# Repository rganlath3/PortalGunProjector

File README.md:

# Portal Gun Embedded Projector

A Portal Gun prop featuring an embedded HDMI projector that displays authentic Portal visuals and sounds. This project combines 3D printing, electronics, and software to create a realistic prop that doubles as a portable projector. The portal gun is from popular Valve videogame, Portal / Portal 2.

<!-- TABLE OF CONTENTS -->
## Table of Contents

<details>
<summary>Table of Contents</summary>

1. [About The Project](#about-the-project)
    - [Design Tools & Requirements](#design-tools--requirements)
        - [Software Requirements](#software-requirements)
        - [Hardware Requirements](#hardware-requirements)
2. [Hardware Development](#hardware-development)
    - [Bill of Materials](#bill-of-materials)
    - [Hardware Used](#hardware-used)
    - [3D Printing the Model](#3d-printing-the-model)
    - [3D Printing Specifications](#3d-printing-specifications)
    - [Model Prep](#model-prep)
    - [Electrical Interconnect Diagram](#electrical-interconnect-diagram)
    - [PCB](#pcb)
    - [Wiring](#wiring)
    - [Power](#power)
3. [Software Development](#software-development)
4. [Getting Started](#getting-started)
    - [Prerequisites](#prerequisites)
    - [Installation](#installation)
    - [Common Issues](#common-issues)
5. [Assets](#assets)
    - [Audio](#audio)
    - [Video](#video)
6. [Roadmap](#roadmap)
7. [Contributing & Donations](#contributing--donations)
8. [License](#license)
9. [Contact](#contact)

</details>

<!-- ABOUT THE PROJECT -->
## About The Project
The idea was to take 3D printing a Portal Gun Prop to the next level of realism. My brother inspired me to create a Prop Portal Gun with an full HDMI Projector inside of the prop. When activated, it displays authentic Portal visuals, produces game-accurate sound effects through integrated speakers, and displays LED effects. The project combines 3D printing, electronics, and software development to create a prop that's both visually accurate and practically useful as a portable projector.

### Design Tools & Requirements

#### Software Requirements
- Python 3.9+ (Programming Language for RPi)
- Raspberry Pi OS Debian v12 (64-bit)
- VS Code (Programming IDE)
- Autodesk Fusion360 (Free CAD Software)
- KiCAD 7 (Open Source PCB Design Software)
- Ultimaker Cura (Free 3D Slicing Software)

#### Hardware Requirements
- Raspberry Pi 4 (8GB RAM recommended)
- 32GB+ SD Card
- 12V Power Supply or 4S Lipo Battery Pack

<p align="right">(<a href="#readme-top">back to top</a>)</p>

## Hardware Development

### Bill of Materials
Coming Soon

### Hardware Used
* Raspberry Pi 4 (SBC)
* Custom RPi HAT PCB (Power and GPIO Distribtuion to Screw Terminals) (See PCB Designs)
* Various Capacitors, Resistors, SMD LEDs, JST Connectors, Wire Crimps, etc.
* Various stranded wire lengths and colors: 16AWG, 22AWG.
* 1x DROK 9V-24V to 5V Step Down Buck Converter, 30W (Powers Pi from Battery Input)
* 1x Songhe 10-32V to 21V Step Up Boost Converter, 150W (Powers Projector from Battery Input)
* 1x 16mm Momentary Metal LED Push Button (Orange)
* 1x 16mm Momentary Metal LED Push Button (Blue)
* 2x 2.1mm DC Barrel Jacks Pair (Power Input)
* 2x SPST 20A Heavy Duty Toggle Switch (Projector Power and Pi Power)
* 1x SPST 5A Mini Toggle Switch (LED Power)
* 1x Individually Addressable 5V NeoPixel
* 1x 1ft. RGB COB Individually Addressable 5V LED Strip 
* Portal Gun 3D Design: (found on thingiverse [here](https://www.thingiverse.com/thing:3579224)) 
* My modifications to the Portal Gun 3D Design.
* 3D Printer: Creality CR-10SProV2

### 3D Printing the Model
I used this portal gun design as a basis for my version. This creator put a lot of work into his design so please give him the attention he deserves: [EVARATE Portal Gun](https://www.thingiverse.com/thing:3579224)

### 3D Printing Specifications

#### Print Settings
- Layer Height: 0.2mm
- Infill: 15% for most parts but 100% for finger parts
- Temperature: 210°C (PLA+)
- Build Plate: 60°C
- Support: Required for overhangs
- Material: eSUN PLA+ or equivalent

Besides modifying parts to fit the projector, I also designed an electronics sled to fit the handle base. This is what the DC-DC converters and Raspberry Pi mount to.

### Model Prep
Sanding, filler, painting, etc.

* 3M Acryl Putty, 05096 Green or 05098 Red
* Various Sandpaper and Sanding Sponges
* Dremel
* P95 or Better Respirator (don't cheap out on this)
* Filler & Sandable Primer (I use cheap Rust-Oleum)
* Montana Gold Shock White Pure Spray Paint
* Montana Gold Shock Black Spray Paint
* Spray Max USC 2K High Gloss Clearcoat (Automotive Clearcoat, expensive but worth it!)

Once all the parts have been printed, we need to do some post processing to get the prints as smooth as possible. For my first iteration, I used a dremel to manually cut holes in some parts instead of just CADing them out. (I wasn't sure how things would exactly fit.)

*Note: Anytime we are sanding or spray painting, you MUST be wearing that respirator! 
Also try to handle all the parts with rubber gloves so your fingerprints don't mess up the paint coats.*

Using sanding paper and sponges I used the following grits:
120->220->320->400 using spot putty where needed. Anything above 320 grit should be wet sanded. Then 2x coats of fillable primer spray paint. Then 400 grit. Then 1x coat of fillable primer. Then one more 400 grit. Then 600 grit. Then apply desired paint color (black and white) base coat in many light coats. (3-5 coats) I'd like to try to find an alternate to Montana Gold.

Once fully dried, use a damp sponge and wipe the parts. Use 1000 grit to sand down the base coat. 

Optional: Using citadel paints or any acrylic paints, add weathering, scuff marks, or damage. I ended up using a metal file and creating scratches. I finely dry brushed silver paint onto the black parts to create a metallic highlight effect. I also added a white line on the top white part.

Once finished painting, we can now apply layers of clearcoat in a very well ventilated area. This 2K stuff is really toxic so be careful. I ended up using rust-oleum 2x ultracover clear instead which gave a good result but not as nice as 2k would have been. I used gloss clear coat on the white parts and black arms. I used matte clear coat on the black parts. Once fully cured, assembly can begin.

### Electrical Interconnect Diagram

### PCB
I designed a Raspberry Pi Hat PCB that handles powering the board (via 5V pins), powering LEDs, and acting as GPIO inputs/outputs for button inputs and driving neopixels. See Mk2 design for the latest. If I had a chance for another iteration, I would add slotted holes in the center section for the placement of a low profile fan for cooling the raspberry pi.

### Wiring
I used 22AWG and 16AWG for all wiring in the system. 22AWG was used for neopixels and GPIO pins while 16AWG was used for all power lines. 
* Red - Power
* Black - GND
* Green - Data / GPIO

### Power
I have two separate power circuits: Pi and Projector.

The Pi Circuit runs on 5V. It powers the neopixels, raspberry pi, and push button LEDs.
* Input Voltage: 12V
* Converted Voltage: 5V
* Average Wattage (Script Running): 4.1W
* Theorhetical Max Load: 
* Safety Factor (Max Power * 1.25W): 7W
* Battery Required for 2 hour battery life:

The Projector Circuit runs on 21V. It powers the projector and it's internal speakers.
* Input Voltage: 12V
* Converted Voltage: 21V
* Average Watage (Lamp On): 41.46W
* Theorhetical Max Load:
* Safety Factor (Max Power * 1.25W): 53W
* Battery Required for 2 hour battery life:

## Software Development
I am familiar using an Arduino or other MCU to solve all my hardware integration problems. In the past I've used Arduinos + Raspberry Pis when needed (such as for ROS projects). For this project, I wanted to challenge myself to not use any MCUs and to only use the raspberry pi GPIO pins to interact with switches and LED control. It brought up some fun compatibility issues that prevented me from using a Raspberry Pi 5 until libraries were updated. 

***Disclaimer: I am an electrical engineer, so apologies for the chaos that is my programming.***

<!-- GETTING STARTED -->
## Getting Started

* Install Raspberry Pi OS with Desktop (Debian v12) (64-bit)
  * we will use the desktop version for initial setup then switch to the CLI for actual operation. This saves time when troubleshooting things like VLC issues.
* Copy this repo to any desired folder. 
  * For reference, my filepath was: */home/aperture/Documents/PortalGunProjector*

### Prerequisites
*Note: Since Neopixel Usage requires root priviledges, make sure your environment path is configured accordingly. I recommend installing all these python libraries as root (sudo command). It is possible to run sudoless but it requires using only GPIO10 for LEDs*

```bash
# Update System
sudo apt update && sudo apt upgrade -y

# Install Required Packages
sudo apt install git python3-pip vlc -y

# Install Python Dependencies

# Raspberry PI GPIO Control
sudo pip3 install gpiozero

# NeoPixel Drivers
sudo pip3 install adafruit-circuitpython-neopixel

# Pygame
sudo pip3 install pygame

# VLC
sudo apt install vlc

# VLC Python Bindings
sudo pip3 install python-vlc
```

### Installation

1. If you haven't already, clone the repo, to a directory such as: */home/username/Documents/PortalGunProjector*

   ```sh
   git clone https://github.com/rganlath3/PortalGunProjector.git
   ```
2. Install prequisites listed above.

3. Run each test script to test functionality as you build, then run launch.py

<p align="right">(<a href="#readme-top">back to top</a>)</p>

### Common Issues

1. LED Control Fails
```bash
# Check permissions
sudo usermod -a -G gpio $USER
# Reboot required after permission change
```

2. Video Playback Issues
- Ensure micro HDMI port used is closest to USB-C power connector.
- Check video codec compatibility
- Verify file permissions

## Assets

### Audio
The portal gun plays audio out of the hdmi audio output via the projector speakers. Everytime a button is pressed, a random soundclip from a list will play to add some variety to mashing buttons. All audio files are in the "Sounds" folder and are extracted from in game. I do not own these files.

### Video
On bootup a random video and audio line will play as an initialization. On button presses, a random sized orange or blue portal video will play on loop. I manually created these videos by screen recording Garry's Mod and careful editing. Bootup videos are sourced from Portal Gameplay and Trailers from Value and are not owned by me. 

<!-- ROADMAP -->
## Roadmap
- [x] CAD Small Projector
- [x] Modify Portal Gun Designs
- [x] Design electrical interconnect
- [x] 3D Print all parts
- [x] Sanding and post processing on parts
- [x] Painting all parts
- [x] Redesign electrical interconnect
- [x] Create Electronics Sled
- [x] Create wiring harness
- [x] Test LED effects
- [x] Integrate pushbuttons into programming
- [x] Create portal and bootup videos
- [x] Configure code to run on startup
- [x] Add Visual Documentation to GitHub
- [x] Assemble Portal Gun
- [x] Final tests with benchtop power supply
- [ ] Add magnets and external cables
- [ ] Create Battery Harness

<p align="right">(<a href="#readme-top">back to top</a>)</p>

<!-- CONTRIBUTING -->
## Contributing & Donations

Any donation helps to support parts for future open source projects!
[Buy Me a Coffee ☕](https://www.buymeacoffee.com/rganlath)

Contributions are what make the open source community such an amazing place to learn, inspire, and create. Any contributions you make are **greatly appreciated**.

If you have a suggestion that would make this better, please fork the repo and create a pull request. You can also simply open an issue with the tag "enhancement".
Don't forget to give the project a star! Thanks again!

<p align="right">(<a href="#readme-top">back to top</a>)</p>

<!-- LICENSE -->
## License
The contents of this project itself is licensed under CERN-OHL-S-2.0 and the underlying source code used for programming the raspberry pi is licensed under GNU GPLv3. Both of these licenses require attribution.

<p align="right">(<a href="#readme-top">back to top</a>)</p>

<!-- CONTACT -->
## Contact

Ranil Ganlath - ranil.ganlath@gmail.com

Project Link: [https://github.com/rganlath3/PortalGunProjector](https://github.com/rganlath3/PortalGunProjector)

<p align="right">(<a href="#readme-top">back to top</a>)</p>

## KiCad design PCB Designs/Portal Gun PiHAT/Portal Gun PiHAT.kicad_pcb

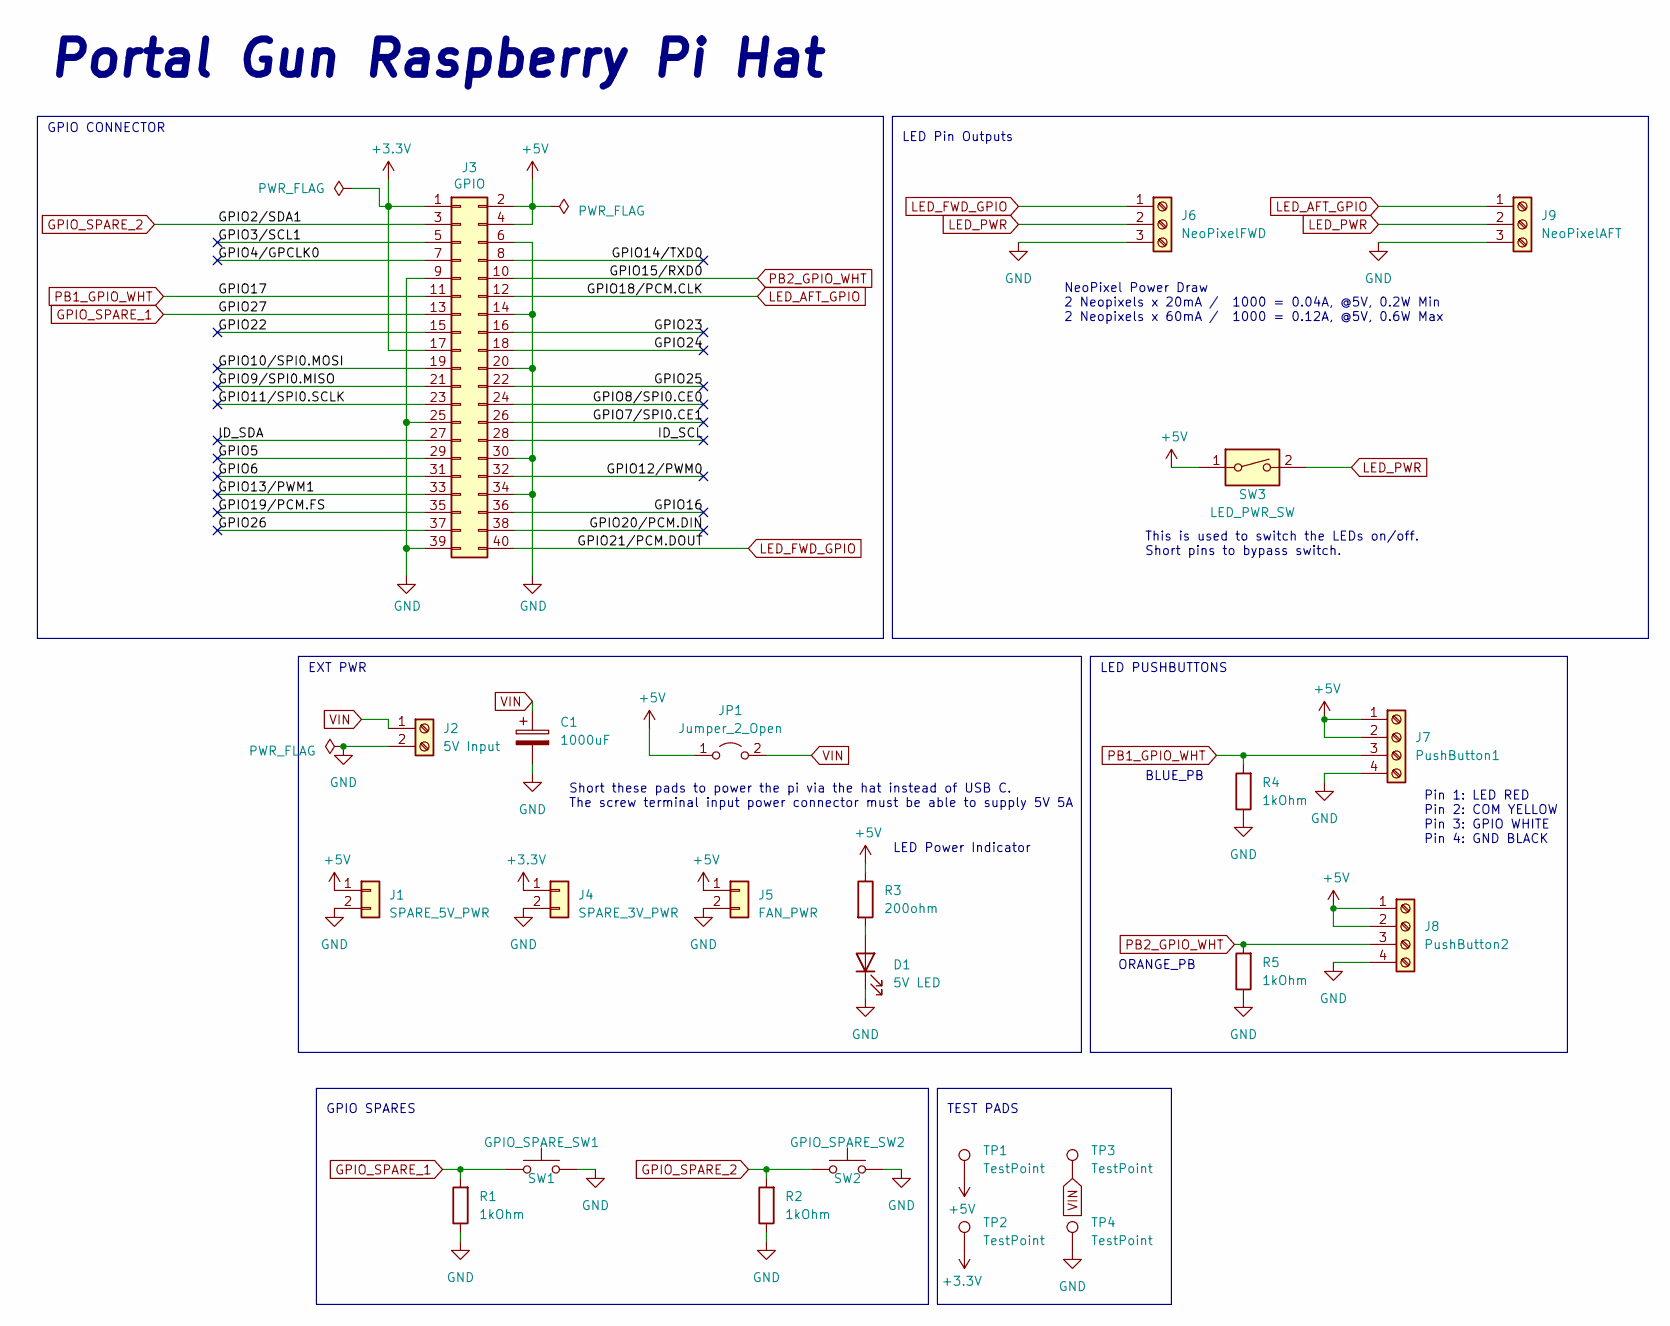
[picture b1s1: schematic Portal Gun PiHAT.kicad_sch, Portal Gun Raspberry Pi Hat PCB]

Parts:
C1: 1000uF; C_Radial_D10.0mm_H16.0mm_P5.00mm
D1: 5V LED; LED_D3.0mm
J1: SPARE_5V_PWR; PinHeader_1x02_P2.54mm_Vertical
J2: 5V Input; TerminalBlock_Phoenix_MKDS-1,5-2_1x02_P5.00mm_Horizontal
J3: GPIO; PinSocket_2x20_P2.54mm_Vertical
J4: SPARE_3V_PWR; PinHeader_1x02_P2.54mm_Vertical
J5: FAN_PWR; PinHeader_1x02_P2.54mm_Vertical
J6: NeoPixelFWD; TerminalBlock_Phoenix_MKDS-1,5-3_1x03_P5.00mm_Horizontal
J7: PushButton1; TerminalBlock_Phoenix_MKDS-1,5-4_1x04_P5.00mm_Horizontal
J8: PushButton2; TerminalBlock_Phoenix_MKDS-1,5-4_1x04_P5.00mm_Horizontal
J9: NeoPixelAFT; TerminalBlock_Phoenix_MKDS-1,5-3_1x03_P5.00mm_Horizontal
JP1: Jumper_2_Open; SolderJumper-2_P1.3mm_Open_Pad1.0x1.5mm
R1, R2, R4, R5: 1kOhm; R_1206_3216Metric_Pad1.30x1.75mm_HandSolder
R3: 200ohm; R_1206_3216Metric_Pad1.30x1.75mm_HandSolder
SW1: GPIO_SPARE_SW1; PinHeader_1x02_P2.54mm_Vertical
SW2: GPIO_SPARE_SW2; PinHeader_1x02_P2.54mm_Vertical
SW3: LED_PWR_SW; PinHeader_1x02_P2.54mm_Vertical
TP1, TP2, TP3, TP4: TestPoint; TestPoint_Pad_D1.0mm

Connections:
+3V3: J3.1, J3.17, J4.1, TP2.1
+5V: J1.1, J3.2, J3.4, J5.1, J7.1, J7.2, J8.1, J8.2, JP1.1 (A), R3.1, SW3.1, TP1.1
/GPIO3/SCL1: J3.5
/GPIO4/GPCLK0: J3.7
/GPIO5: J3.29
/GPIO6: J3.31
/GPIO7/SPI0.CE1: J3.26
/GPIO8/SPI0.CE0: J3.24
/GPIO9/SPI0.MISO: J3.21
/GPIO10/SPI0.MOSI: J3.19
/GPIO11/SPI0.SCLK: J3.23
/GPIO12/PWM0: J3.32
/GPIO13/PWM1: J3.33
/GPIO14/TXD0: J3.8
/GPIO16: J3.36
/GPIO19/PCM.FS: J3.35
/GPIO20/PCM.DIN: J3.38
/GPIO22: J3.15
/GPIO23: J3.16
/GPIO24: J3.18
/GPIO25: J3.22
/GPIO26: J3.37
/ID_SCL: J3.28
/ID_SDA: J3.27
GND: C1.2, D1.1 (K), J1.2, J2.2, J3.6, J3.9, J3.14, J3.20, J3.25, J3.30, J3.34, J3.39, J4.2, J5.2, J6.3, J7.4, J8.4, J9.3, R1.1, R2.1, R4.1, R5.1, SW1.2, SW2.2, TP4.1
GPIO_SPARE_1: J3.13, R1.2, SW1.1
GPIO_SPARE_2: J3.3, R2.2, SW2.1
LED_AFT_GPIO: J3.12, J9.1
LED_FWD_GPIO: J3.40, J6.1
LED_PWR: J6.2, J9.2, SW3.2
unnamed: D1.2 (A), R3.2
PB1_GPIO_WHT: J3.11, J7.3, R4.2
PB2_GPIO_WHT: J3.10, J8.3, R5.2
VIN: C1.1, J2.1, JP1.2 (B), TP3.1

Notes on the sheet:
LED Power Indicator
This is used to switch the LEDs on/off. Short pins to bypass switch.
GPIO CONNECTOR
LED PUSHBUTTONS
Portal Gun Raspberry Pi Hat
NeoPixel Power Draw 2 Neopixels x 20mA / 1000 = 0.04A, @5V, 0.2W Min 2 Neopixels x 60mA / 1000 = 0.12A, @5V, 0.6W Max
BLUE_PB
ORANGE_PB
LED Pin Outputs
GPIO SPARES
Short these pads to power the pi via the hat instead of USB C. The screw terminal input power connector must be able to supply 5V 5A
Pin 1: LED RED Pin 2: COM YELLOW Pin 3: GPIO WHITE Pin 4: GND BLACK
TEST PADS
EXT PWR

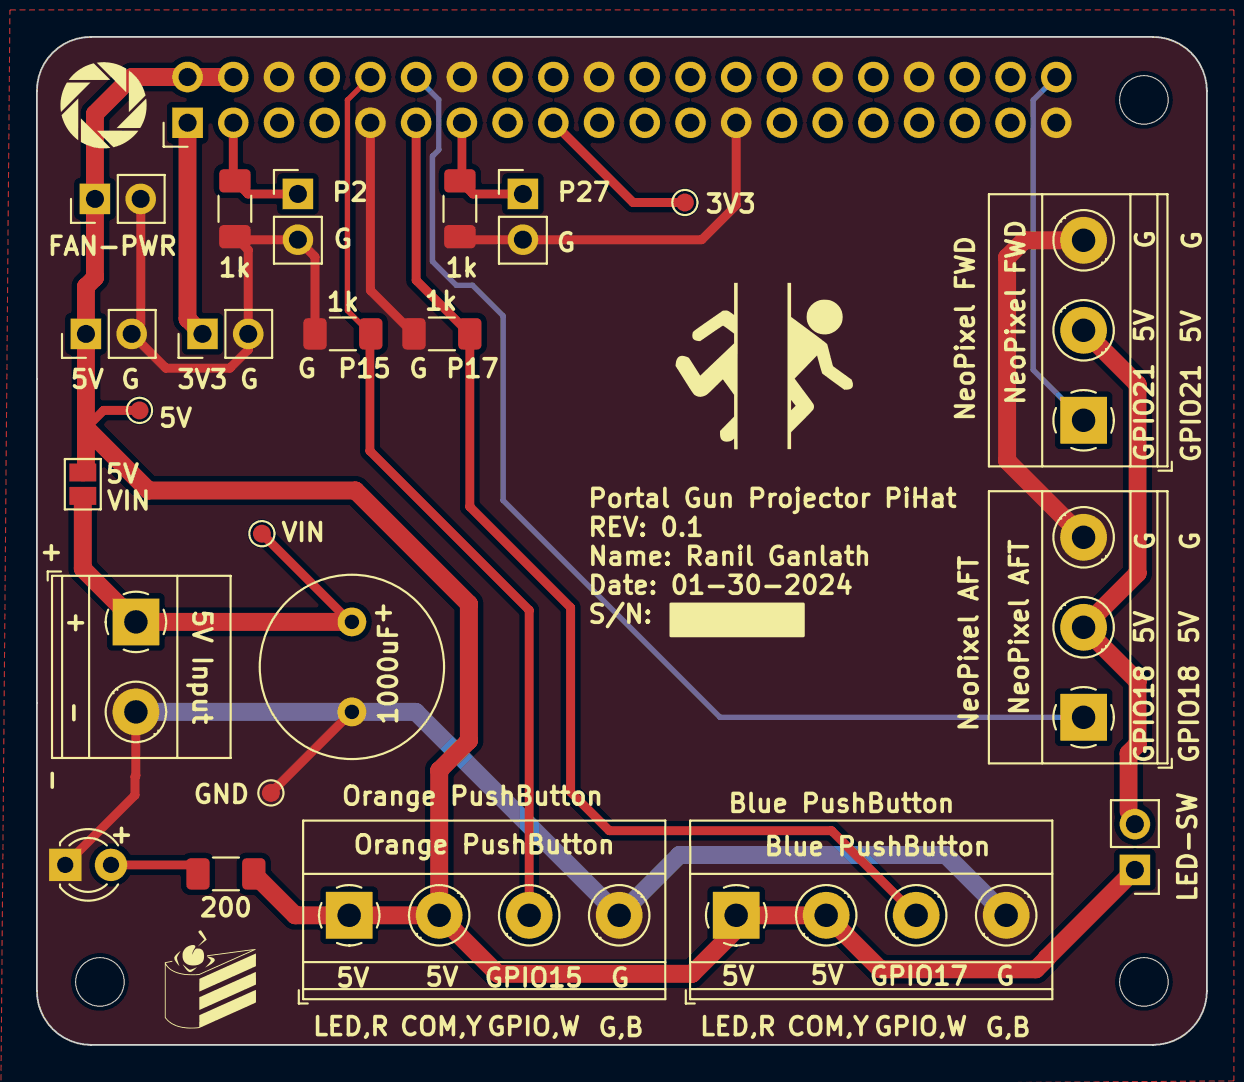
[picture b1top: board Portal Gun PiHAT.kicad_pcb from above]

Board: 2 copper layers, 65.0 x 56.0 mm, 27 parts (1 on the bottom side), 12 nets.

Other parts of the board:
MH2, MH3, MH4: MountingHole_2.7mm_M2.5

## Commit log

2024-01-23 Initial Project Creation
2024-01-23 Added parts from prior kiKAD projects
2024-01-25 schematic updates
2024-01-31 KiCad PCBs Finalized
2024-01-31 Audio File Upload
2024-01-31 Test Script Creation
2024-02-23 PCB Design Updates to fix name formatting and 3V GPIO correction on pushbuttons
2024-03-20 Updated for longer LED chain
2024-03-20 Button Fixes
2024-03-26 Renamed Audio Files
2024-03-26 Added new led animations
2024-03-27 Added new animations and audio sounds
2024-03-27 Added new sounds effects
2024-03-28 Changed format of some sounds to be .wav
2024-03-29 Incorporated new bootup sounds, need to add queue thingy.
2024-03-29 Added bootup animation based on sound file played.
2024-04-03 Created scripts that start on bootup.
2024-04-03 Changed naming convention and added comments
2024-04-03 Starting Video PlayBack Tests
2024-04-03 Portal Looping Animations
2024-04-04 Testing VideoPlayBack. Need to find VLC commands or alt.
2024-04-08 Testing out python-vlc library.
2024-04-09 finally got vlc working smoothly, just need to roll into main script.
2024-04-09 working but no fullscreen
2024-04-09 it works! just needs cleanup
2024-04-10 Finally got VLC fully working with audio track
2024-04-10 Updated launch script to handle if pi is in cli or gui mode accordingly.
2024-04-10 Testing PathLib
2024-04-11 Created bootup videos
2024-04-11 Added Bootup Video and Relative File Paths
2024-04-11 Debug command to turn off LEDs added
2024-04-11 trying to make code launch on bootup in both cli and desktop environments
2024-04-12 Updated with model prep info.
2024-04-12 Updates to readme and project cleanup.
2024-12-05 updates to startup script.
2024-12-06 Updates to the readme.
2025-02-01 Updated boot videos to be all from in game or trailers.
2025-02-01 Added PCB visual documentation
2025-02-02 Added CAD screenshots and initial build pictures.
2025-02-02 fixing relative paths
2025-02-02 testing image embed
2025-02-02 Renamed images for readme embed.
2025-02-08 Added visuals and updated readme.
2025-02-08 readme image updates
2025-02-08 Revisions to readme
2025-02-08 Revised Readme

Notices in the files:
README.md:
Hardware License: CERN-OHL-S-2.0
Software License: GPL v3
